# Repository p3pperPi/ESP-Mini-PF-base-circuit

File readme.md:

# 概要
ESP32を使用して、DCブラシモータを使用したライントレースをするための基板です。

# 回路図

# 機能
## 電源
J1の PHコネクタ、もしくは J3の XT60コネクタに電源を接続してください。
J1の PHコネクタを使用する際は、J2の PHコネクタにスイッチをつないでください。

入力可能な電圧の範囲はは ** 30V** です。

また、JP17をショートすることで、モータ電源にUSB 5Vを使用することが可能です。
ただし、JP17をショートした状態で電源コネクタに5V以外の電圧をかけると、接続した機器が破損します。
**JP17をショートさせた際は、絶対に電源コネクタから給電は行わないでください。**
なお、JP17にはダイオードを入れて逆流防止を行うことも可能です。その際は、[SBM245L](https://akizukidenshi.com/catalog/g/g117439/)を使用してください。

入力電源は、DCDCコンバータモジュール[CN39033A](https://japanese.alibaba.com/product-detail/CN3903-3A-Mini-Buck-Step-Down-1600380707339.html)を使用して5Vまで電圧を下げられます。

| 項目             | 値  | 単位 |
| ---------------- | --- | ---- |
| 最大定格入力電圧 | 30  | V    |
| 出力電流(Max.)   | 3   | A    |

上で生成された5Vから、[UZ1085L-22-TN3-R](https://www.lcsc.com/product-detail/Low-Dropout-Regulators-LDO_UZ1085L-AD-TN3-R_C146666.html)を使用し、マイコンへの電源供給を行います。
| 項目             | 値  | 単位 |
| ---------------- | --- | ---- |
| 最大定格入力電圧 | 18  | V    |
| 最大電流(Typ.)   | 4   | A |

## マイコン
ESP32-WROOM-32を使用します。  
[CH340X](https://www.lcsc.com/product-detail/USB-Converters_WCH-Jiangsu-Qin-Heng-CH340X_C3035748.html?s_z=n_CH340X)を使用した書き込み回路を持ちます。

## DCブラシモータ
モータドライバIC[CP3119MDTR](https://www.lcsc.com/product-detail/Brushed-DC-Motor-Drivers_XBLW-CP3119MDTR-XBLW_C42395499.html)を使用して、DCモータを制御します。

| 項目                  | 値       | 単位       |
| --------------------- | -------- | ---------- |
| 最大定格電圧          | 32       | V          |
| 最大定格電流          | 8.0      | A          |
| 推奨電源電圧範囲      | 3.0~30.0 | V          |
| 推奨最大電流          | 6.0      | A          |
| FETオン抵抗 (load=1A) | 80       | m $\Omega$ |
| FETオン抵抗 (load=3A) | 110      | m $\Omega$ |

## エンコーダ
A/B相のシングルエンドエンコーダをカウントします。エンコーダの電源電圧と信号入力は5Vです。
[TXB0104RUT](https://lcsc.com/product-detail/translators-level-shifters_texas-instruments-txb0104rutr_C105266.html)により、5V信号を3.3Vに変換してESP32に信号を入力します。
パルス入力ピンは、ソルダジャンパ(JP2 ~ 5)によりプルアップが可能です。
プルアップの有無については、[ジャンパの機能](#ジャンパの機能)を参照してください。

## 汎用IO
サーボモータ、センサ入力等のための、汎用のIOです。
ピンアサインは下記の通りです。

| ピン | 機能   |
| ---- | ------ |
| 1    | IOピン |
| 2    | Vs     |
| 3    | GND    |

ピン番号は、[ピンアサイン](#ピンアサイン)を参照してください。

Vsは、ソルダジャンパ(JP6 ~ 9)により電圧を選択可能です。
選択される電圧は、[ジャンパの機能](#ジャンパの機能)を参照してください。

## フォトリフレクタ
[ITR8307/S17/TR8(B)](https://www.lcsc.com/product-detail/Reflective-Optical-Interrupters_Everlight-Elec-ITR8307-S17-TR8-B_C81632.html?s_z=n_ITR8307-S17) を3つ搭載し、テープの判定を行います。

また、外付けのLED・フォトトランジスタを使用することも可能です。いずれも外形3mmの砲弾型のものを使用してください。

使用するフォトリフレクタの選択は、JP10～JP15 を使用してください。

## LED
3mm砲弾型LEDを4つ搭載可能です。  
D2は、電源投入時に点灯します。  
D3, D4, D5はESP32から点灯/消灯 を管理可能です。

# ピンアサイン

ESP32-WROOM-32のピンアサインは下記の通りです。

| ピン | IO pin          | 機能                 | IN/OUT       |
| ---- | --------------- | -------------------- | ------------ |
| 27   | IO16            | モータL出力1         | OUT (PWM)    |
| 28   | IO17            | モータL出力2         | OUT (PWM)    |
| 30   | IO18            | モータR出力1         | OUT (PWM)    |
| 31   | IO19            | モータR出力2         | OUT (PWM)    |
| 16   | IO13            | エンコーダL入力1     | IN (PWM)     |
| 13   | IO14            | エンコーダL入力2     | IN (PWM)     |
| 10   | IO25            | エンコーダR入力1     | IN (PWM)     |
| 11   | IO26            | エンコーダR入力2     | IN (PWM)     |
| 34   | IO3/RxD0        | PCとのUART RxD       | IN (COM.)    |
| 35   | IO1/TxD0        | PCとのUART TxD       | OUT (COM.)   |
| 25   | IO0             | Boot                 | -            |
| 9    | IO33            | ラインセンサ1        | IN(Analog)   |
| 6    | IO34            | ラインセンサ2        | IN(Analog)   |
| 8    | IO35            | ラインセンサ3        | IN(Analog)   |
| 33   | IO21            | LED 赤               | OUT(Digital) |
| 36   | IO22            | LED 黄               | OUT(Digital) |
| 37   | IO23            | LED 緑               | OUT(Digital) |
| 8    | IO32            | 汎用IO 0             | IN/OUT       |
| 12   | IO27            | 汎用IO 1             | IN/OUT       |
| 26   | IO4             | 汎用IO 2             | IN/OUT       |
| 29   | IO5             | 汎用IO 3(プルアップ) | IN/OUT       |
| 4    | IO36(SENSOR_VP) | 電源電圧監視(1/10)   | IN(Analog)   |

# ジャンパの機能

ジャンパにより、機能を切り替えることができます。

| ジャンパ | 機能             | モード1  | 機能1                                  | モード2  | 機能2                                 | デフォルト | 備考                                     |
| -------- | ---------------- | -------- | -------------------------------------- | -------- | ------------------------------------- | ---------- | ---------------------------------------- |
| JP1      | Power_SW_Disable | オープン | J2 パワースイッチが有効                | ショート | J2 パワースイッチが無効(常時ショート) | オープン   | -                                        |
| JP2      | L1_PU            | オープン | エンコーダL1の入力は電圧入力           | ショート | エンコーダL1の入力をプルアップ(1k)    | オープン   | -                                        |
| JP3      | L2_PU            | オープン | エンコーダL2の入力は電圧入力           | ショート | エンコーダL2の入力をプルアップ(1k)    | オープン   | -                                        |
| JP4      | R1_PU            | オープン | エンコーダR1の入力は電圧入力           | ショート | エンコーダR1の入力をプルアップ(1k)    | オープン   | -                                        |
| JP5      | R2_PU            | オープン | エンコーダR2の入力は電圧入力           | ショート | エンコーダR2の入力をプルアップ(1k)    | オープン   | -                                        |
| JP6      | Vs_SEL0          | 3.3      | 汎用入力J9 の2番ピンを3.3Vにする       | Vin      | 汎用入力J9 の2番ピンをVinにする       | オープン   | オープンだと2番ピンはNC                  |
| JP7      | Vs_SEL1          | 3.3      | 汎用入力J10 の2番ピンを3.3Vにする      | Vin      | 汎用入力J10 の2番ピンをVinにする      | オープン   | オープンだと2番ピンはNC                  |
| JP8      | Vs_SEL2          | 3.3      | 汎用入力J11 の2番ピンを3.3Vにする      | Vin      | 汎用入力J11 の2番ピンをVinにする      | オープン   | オープンだと2番ピンはNC                  |
| JP9      | Vs_SEL3          | 3.3      | 汎用入力J12 の2番ピンを3.3Vにする      | Vin      | 汎用入力J12 の2番ピンをVinにする      | オープン   | オープンだと2番ピンはNC                  |
| JP10     | LED_SEL1         | SMD      | ラインセンサ(U8)の LEDを有効化         | DIP      | D6 のLEDを有効化                      | オープン   | オープンだとU8, D6いずれのLEDも光らない  |
| JP11     | PT_SEL1          | SMD      | SENSOR1 の入力をラインセンサU8 にする  | DIP      | SENSOR1 の入力をQ1 にする             | オープン   | オープンだとSENSOR1 はN.C.               |
| JP12     | LED_SEL2         | SMD      | ラインセンサ(U9)の LEDを有効化         | DIP      | D7 のLEDを有効化                      | オープン   | オープンだとU9, D7いずれのLEDも光らない  |
| JP13     | PT_SEL2          | SMD      | SENSOR2 の入力をラインセンサU9 にする  | DIP      | SENSOR2 の入力をQ2 にする             | オープン   | オープンだとSENSOR2 はN.C.               |
| JP14     | LED_SEL2         | SMD      | ラインセンサ(U10)の LEDを有効化        | DIP      | D8 のLEDを有効化                      | オープン   | オープンだとU10, D8いずれのLEDも光らない |
| JP15     | PT_SEL2          | SMD      | SENSOR3 の入力をラインセンサU10 にする | DIP      | SENSOR3 の入力をQ1 にする             | オープン   | オープンだとSENSOR3 はN.C.               |
| JP16     | Reseet           | オープン | 通常動作                               | ショート | リセット                              | オープン   | スイッチ取付可                           |
| JP17     | USB＿Vs          | オープン | 外部電源をモータ電源とする             | ショート | USB電源をモータ電源とする             | オープン   | ショートの代わりにダイオードを使用可     |

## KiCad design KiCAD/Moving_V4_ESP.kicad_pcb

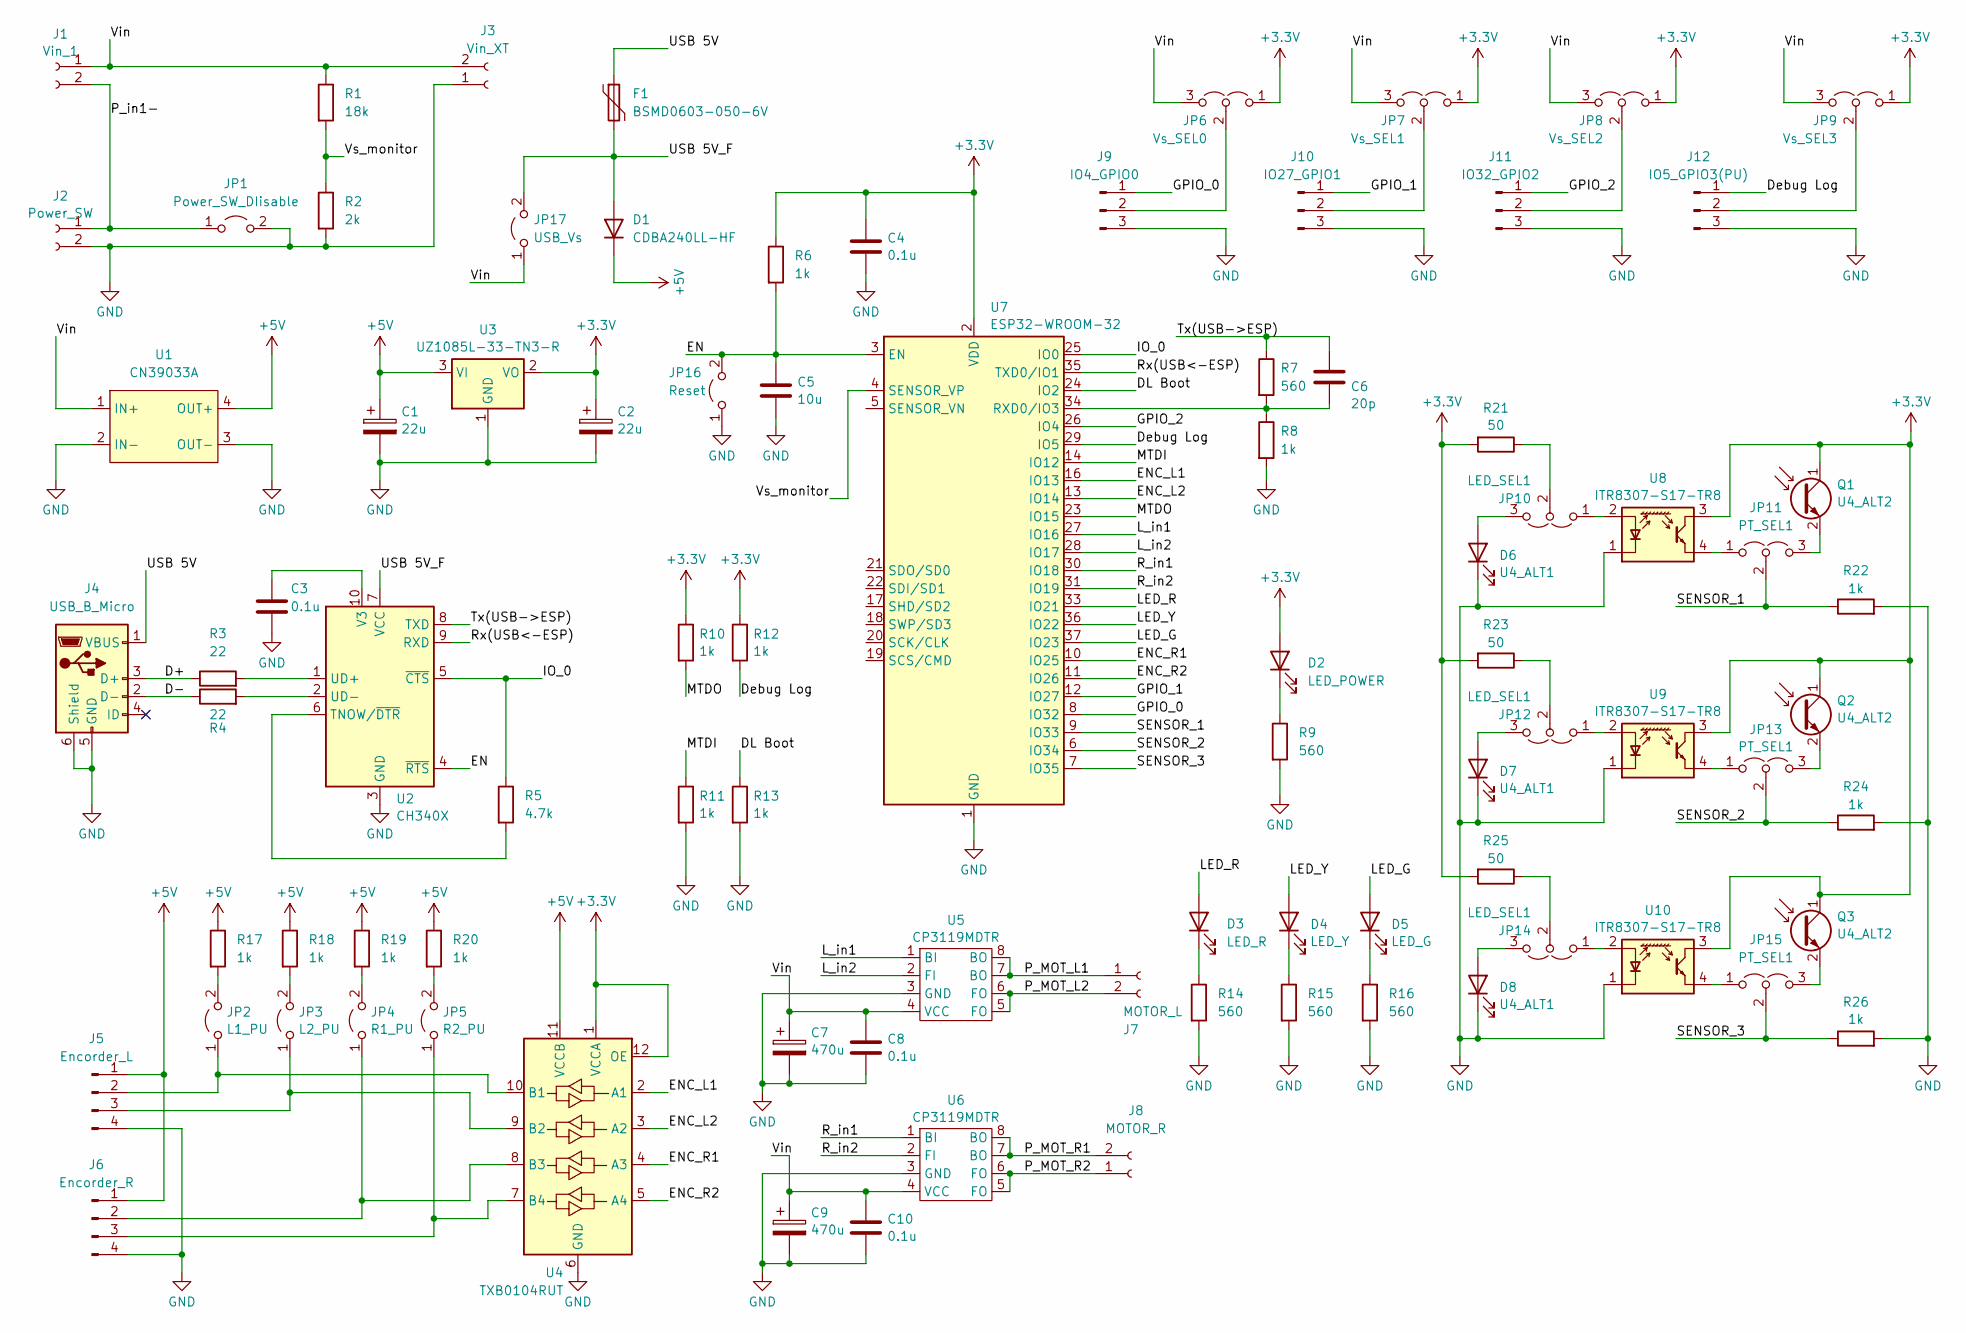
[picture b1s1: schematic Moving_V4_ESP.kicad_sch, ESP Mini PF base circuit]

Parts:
C1, C2: 22u; CP_Radial_D5.0mm_P2.00mm; LCSC x
C3, C4, C8, C10: 0.1u; C_0402_1005Metric; LCSC C77020
C5: 10u; C_0402_1005Metric; LCSC C76991
C6: 20p; C_0402_1005Metric; LCSC C76959
C7, C9: 470u; CP_Radial_D8.0mm_P3.50mm; LCSC x
D1: CDBA240LL-HF; D_SMA; LCSC C2886093
D2: LED_POWER; LED_D3.0mm; LCSC x
D3: LED_R; LED_D3.0mm; LCSC x
D4: LED_Y; LED_D3.0mm; LCSC x
D5: LED_G; LED_D3.0mm; LCSC x
D6, D7, D8: U4_ALT1; LED_D3.0mm; LCSC x
F1: BSMD0603-050-6V; Fuse_0603_1608Metric; LCSC C883095
J1: Vin_1; JST_PH_B2B-PH-K_1x02_P2.00mm_Vertical; LCSC x
J2: Power_SW; JST_PH_B2B-PH-K_1x02_P2.00mm_Vertical; LCSC x
J3: Vin_XT; AMASS_XT60-M_1x02_P7.20mm_Vertical; LCSC x
J4: USB_B_Micro; USB_Micro-B_Amphenol_10103594-0001LF_Horizontal; LCSC C428495
J5: Encorder_L; JST_ZH_B4B-ZH-A_1x04_P1.50mm_Vertical; LCSC x
J6: Encorder_R; JST_ZH_B4B-ZH-A_1x04_P1.50mm_Vertical; LCSC x
J7: MOTOR_L; TerminalBlock_bornier-2_P5.08mm; LCSC x
J8: MOTOR_R; TerminalBlock_bornier-2_P5.08mm; LCSC x
J9: IO4_GPIO0; PinHeader_1x03_P2.54mm_Vertical; LCSC x
J10: IO27_GPIO1; PinHeader_1x03_P2.54mm_Vertical; LCSC x
J11: IO32_GPIO2; PinHeader_1x03_P2.54mm_Vertical; LCSC x
J12: IO5_GPIO3(PU); PinHeader_1x03_P2.54mm_Vertical; LCSC x
JP1: Power_SW_DIisable; SolderJumper-2_P1.3mm_Open_RoundedPad1.0x1.5mm; LCSC x
JP2: L1_PU; SolderJumper-2_P1.3mm_Open_RoundedPad1.0x1.5mm; LCSC x
JP3: L2_PU; SolderJumper-2_P1.3mm_Open_RoundedPad1.0x1.5mm; LCSC x
JP4: R1_PU; SolderJumper-2_P1.3mm_Open_RoundedPad1.0x1.5mm; LCSC x
JP5: R2_PU; SolderJumper-2_P1.3mm_Open_RoundedPad1.0x1.5mm; LCSC x
JP6: Vs_SEL0; SolderJumper-3_P1.3mm_Open_RoundedPad1.0x1.5mm; LCSC x
JP7: Vs_SEL1; SolderJumper-3_P1.3mm_Open_RoundedPad1.0x1.5mm; LCSC x
JP8: Vs_SEL2; SolderJumper-3_P1.3mm_Open_RoundedPad1.0x1.5mm; LCSC x
JP9: Vs_SEL3; SolderJumper-3_P1.3mm_Open_RoundedPad1.0x1.5mm; LCSC x
JP10, JP12, JP14: LED_SEL1; SolderJumper-3_P1.3mm_Open_RoundedPad1.0x1.5mm; LCSC x
JP11, JP13, JP15: PT_SEL1; SolderJumper-3_P1.3mm_Open_RoundedPad1.0x1.5mm; LCSC x
JP16: Reset; SolderJumper-2_TVAF06-A020B-R_COMPATIBLE; LCSC x
JP17: USB_Vs; D_DO-41_SOD81_P7.62mm_Horizontal; LCSC x
Q1, Q2, Q3: U4_ALT2; LED_D3.0mm; LCSC x
R1: 18k; R_0402_1005Metric; LCSC C316875
R2: 2k; R_0402_1005Metric; LCSC C173345
R3, R4: 22; R_0402_1005Metric; LCSC C400511
R5: 4.7k; R_0402_1005Metric; LCSC C159885
R6, R8, R10, R11, R12, R13, R17, R18, R19, R20, R22, R24, R26: 1k; R_0402_1005Metric; LCSC C159872
R7, R9, R14, R15, R16: 560; R_0402_1005Metric; LCSC C427239
R21, R23, R25: 50; R_0805_2012Metric; LCSC C2828866
U1: CN39033A; DCDC_Conv_CN39033A; LCSC x
U2: CH340X; MSOP-10_3x3mm_P0.5mm; LCSC C3035748
U3: UZ1085L-33-TN3-R; TO-252-2; LCSC C125622
U4: TXB0104RUT; Texas_R-PUQFN-N12; LCSC C105266
U5, U6: CP3119MDTR; SOP-8_3.9x4.9mm_P1.27mm; LCSC C42395499
U7: ESP32-WROOM-32; ESP32-WROOM-32_39P-TH; LCSC x
U8, U9, U10: ITR8307-S17-TR8; Everlight_ITR1201SR10AR; LCSC C81632

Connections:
+3.3V: C2.1, C4.1, D2.2 (A), JP6.1 (A), JP7.1 (A), JP8.1 (A), JP9.1 (A), Q1.1 (C), Q2.1 (C), Q3.1 (C), R6.1, R10.1, R12.1, R21.2, R23.2, R25.2, U3.2 (VO), U4.1 (VCCA), U4.12 (OE), U7.2 (VDD), U8.3, U9.3, U10.3
+5V: C1.1, D1.1 (K), J5.1, J6.1, R17.1, R18.1, R19.1, R20.1, U1.4 (OUT+), U3.3 (VI), U4.11 (VCCB)
/D+: J4.3 (D+), R3.1
/D-: J4.2 (D-), R4.1
/DL Boot: R13.1, U7.24 (IO2)
/Debug Log: J12.1, R12.2, U7.29 (IO5)
/EN: C5.1, JP16.2 (B), R6.2, U2.4 (~RTS), U7.3 (EN)
/ENC_L1: U4.2 (A1), U7.16 (IO13)
/ENC_L2: U4.3 (A2), U7.13 (IO14)
/ENC_R1: U4.4 (A3), U7.10 (IO25)
/ENC_R2: U4.5 (A4), U7.11 (IO26)
/GPIO_0: J9.1, U7.8 (IO32)
/GPIO_1: J10.1, U7.12 (IO27)
/GPIO_2: J11.1, U7.26 (IO4)
/IO_0: R5.1, U2.5 (~CTS), U7.25 (IO0)
/LED_G: D5.2 (A), U7.37 (IO23)
/LED_R: D3.2 (A), U7.33 (IO21)
/LED_Y: D4.2 (A), U7.36 (IO22)
/L_in1: U5.1 (BI), U7.27 (IO16)
/L_in2: U5.2 (FI), U7.28 (IO17)
/MTDI: R11.1, U7.14 (IO12)
/MTDO: R10.2, U7.23 (IO15)
/P_MOT_L1: J7.1, U5.7 (BO), U5.8 (BO)
/P_MOT_L2: J7.2, U5.5 (FO), U5.6 (FO)
/P_MOT_R1: J8.2, U6.7 (BO), U6.8 (BO)
/P_MOT_R2: J8.1, U6.5 (FO), U6.6 (FO)
/P_in1-: J1.2, J2.1, JP1.1 (A)
/R_in1: U6.1 (BI), U7.30 (IO18)
/R_in2: U6.2 (FI), U7.31 (IO19)
/Rx(USB<-ESP): U2.9 (RXD), U7.35 (TXD0/IO1)
/SENSOR_1: JP11.2 (C), R22.1, U7.9 (IO33)
/SENSOR_2: JP13.2 (C), R24.1, U7.6 (IO34)
/SENSOR_3: JP15.2 (C), R26.1, U7.7 (IO35)
/Tx(USB->ESP): C6.1, R7.1, U2.8 (TXD)
/USB 5V: F1.1, J4.1 (VBUS)
/USB 5V_F: D1.2 (A), F1.2, JP17.2 (B), U2.7 (VCC)
/Vin: C7.1, C8.1, C9.1, C10.1, J1.1, J3.2, JP6.3 (B), JP7.3 (B), JP8.3 (B), JP9.3 (B), JP17.1 (A), R1.1, U1.1 (IN+), U5.4 (VCC), U6.4 (VCC)
/Vs_monitor: R1.2, R2.1, U7.4 (SENSOR_VP)
GND: C1.2, C2.2, C3.2, C4.2, C5.2, C7.2, C8.2, C9.2, C10.2, D6.1 (K), D7.1 (K), D8.1 (K), J2.2, J3.1, J4.5 (GND), J4.6 (Shield), J5.4, J6.4, J9.3, J10.3, J11.3, J12.3, JP1.2 (B), JP16.1 (A), R2.2, R8.2, R9.2, R11.2, R13.2, R14.2, R15.2, R16.2, R22.2, R24.2, R26.2, U1.2 (IN-), U1.3 (OUT-), U2.3 (GND), U3.1 (GND), U4.6 (GND), U5.3 (GND), U6.3 (GND), U7.1 (GND), U7.15 (GND), U7.38 (GND), U7.39 (GND), U8.1 (K), U9.1 (K), U10.1 (K)
unnamed: D2.1 (K), R9.1
unnamed: D3.1 (K), R14.1
unnamed: D4.1 (K), R15.1
unnamed: D5.1 (K), R16.1
unnamed: D6.2 (A), JP10.3 (B)
unnamed: D7.2 (A), JP12.3 (B)
unnamed: D8.2 (A), JP14.3 (B)
unnamed: J5.2, JP2.1 (A), U4.10 (B1)
unnamed: J5.3, JP3.1 (A), U4.9 (B2)
unnamed: J6.2, JP4.1 (A), U4.8 (B3)
unnamed: J6.3, JP5.1 (A), U4.7 (B4)
unnamed: J9.2, JP6.2 (C)
unnamed: J10.2, JP7.2 (C)
unnamed: J11.2, JP8.2 (C)
unnamed: J12.2, JP9.2 (C)
unnamed: JP2.2 (B), R17.2
unnamed: JP3.2 (B), R18.2
unnamed: JP4.2 (B), R19.2
unnamed: JP5.2 (B), R20.2
unnamed: JP10.1 (A), U8.2 (A)
unnamed: JP10.2 (C), R21.1
unnamed: JP11.1 (A), U8.4
unnamed: JP11.3 (B), Q1.2 (E)
unnamed: JP12.1 (A), U9.2 (A)
unnamed: JP12.2 (C), R23.1
unnamed: JP13.1 (A), U9.4
unnamed: JP13.3 (B), Q2.2 (E)
unnamed: JP14.1 (A), U10.2 (A)
unnamed: JP14.2 (C), R25.1
unnamed: JP15.1 (A), U10.4
unnamed: JP15.3 (B), Q3.2 (E)
unnamed: R5.2, U2.6 (TNOW/~DTR)
unnamed: R3.2, U2.1 (UD+)
unnamed: R4.2, U2.2 (UD-)
unnamed: C3.1, U2.10 (V3)
unnamed: C6.2, R7.2, R8.1, U7.34 (RXD0/IO3)

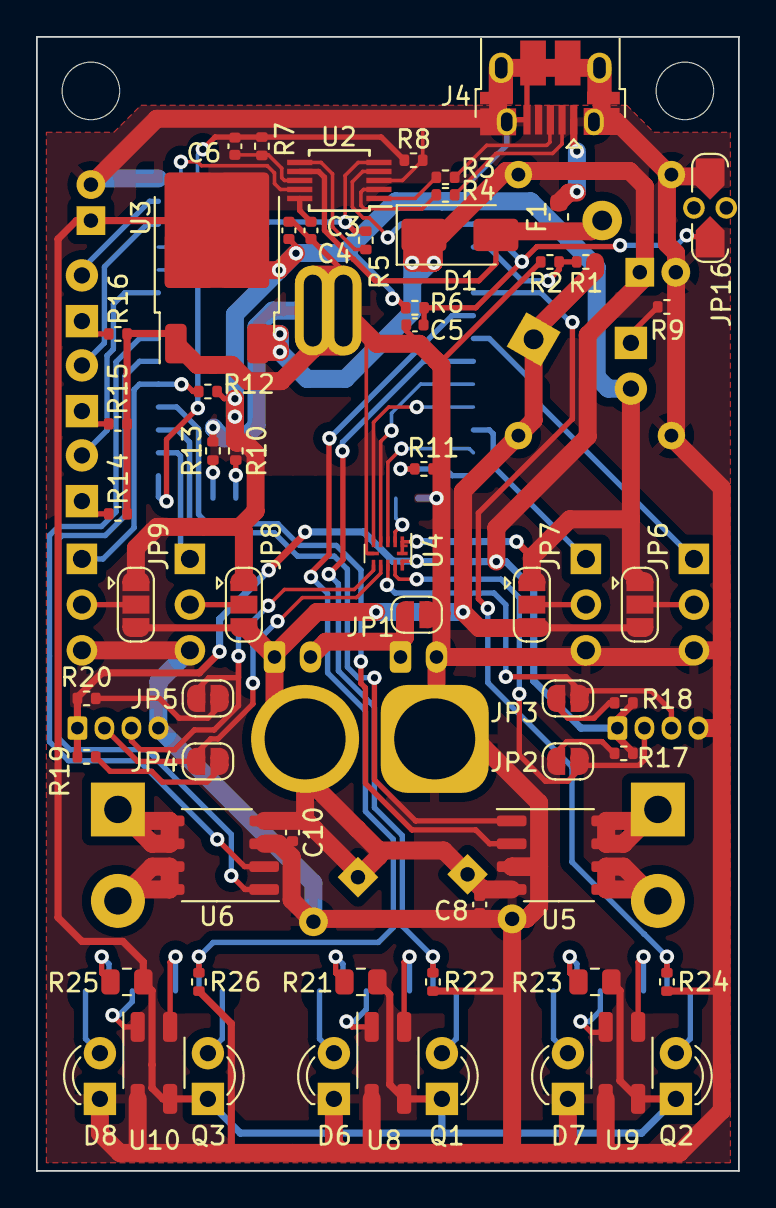
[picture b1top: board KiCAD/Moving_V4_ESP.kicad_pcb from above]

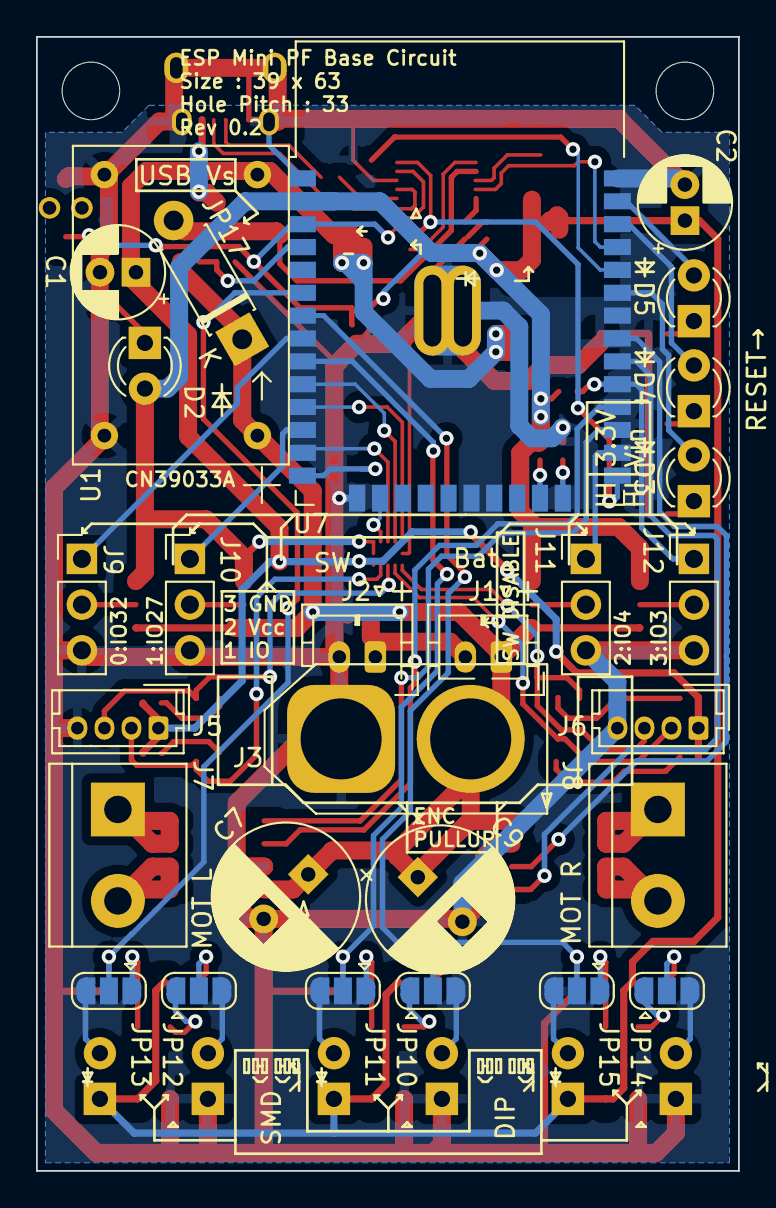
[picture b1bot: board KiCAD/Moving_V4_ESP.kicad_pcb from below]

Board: 2 copper layers, 39.0 x 63.0 mm, 87 parts (28 on the bottom side), 75 nets.

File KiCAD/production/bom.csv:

Designator,Footprint,Quantity,Value,LCSC Part #
"C1, C2",CP_Radial_D5.0mm_P2.00mm,2,22u,x
"C10, C3, C4, C8",0402,4,0.1u,C77020
C5,0402,1,10u,C76991
C6,0402,1,20p,C76959
"C7, C9",CP_Radial_D8.0mm_P3.50mm,2,470u,x
D1,D_SMA,1,CDBA240LL-HF,C2886093
D2,LED_D3.0mm,1,LED_POWER,x
D3,LED_D3.0mm,1,LED_R,x
D4,LED_D3.0mm,1,LED_Y,x
D5,LED_D3.0mm,1,LED_G,x
"D6, D7, D8",LED_D3.0mm,3,U4_ALT1,x
F1,0603,1,"BSMD0603-050-6V
",C883095
J1,JST_PH_B2B-PH-K_1x02_P2.00mm_Vertical,1,Vin_1,x
J10,PinHeader_1x03_P2.54mm_Vertical,1,IO27_GPIO1,x
J11,PinHeader_1x03_P2.54mm_Vertical,1,IO32_GPIO2,x
J12,PinHeader_1x03_P2.54mm_Vertical,1,IO5_GPIO3(PU),x
J2,JST_PH_B2B-PH-K_1x02_P2.00mm_Vertical,1,Power_SW,x
J3,AMASS_XT60-M_1x02_P7.20mm_Vertical,1,Vin_XT,x
J4,USB_Micro-B_Amphenol_10103594-0001LF_Horizontal,1,USB_B_Micro,C428495
J5,JST_ZH_B4B-ZH-A_1x04_P1.50mm_Vertical,1,Encorder_L,x
J6,JST_ZH_B4B-ZH-A_1x04_P1.50mm_Vertical,1,Encorder_R,x
J7,TerminalBlock_bornier-2_P5.08mm,1,MOTOR_L,x
J8,TerminalBlock_bornier-2_P5.08mm,1,MOTOR_R,x
J9,PinHeader_1x03_P2.54mm_Vertical,1,IO4_GPIO0,x
JP1,SolderJumper-2_P1.3mm_Open_RoundedPad1.0x1.5mm,1,Power_SW_DIisable,x
"JP10, JP12, JP14",SolderJumper-3_P1.3mm_Open_RoundedPad1.0x1.5mm,3,LED_SEL1,x
"JP11, JP13, JP15",SolderJumper-3_P1.3mm_Open_RoundedPad1.0x1.5mm,3,PT_SEL1,x
JP16,SolderJumper-2_TVAF06-A020B-R_COMPATIBLE,1,Reset,x
JP17,D_DO-41_SOD81_P7.62mm_Horizontal,1,USB_Vs,x
JP2,SolderJumper-2_P1.3mm_Open_RoundedPad1.0x1.5mm,1,L1_PU,x
JP3,SolderJumper-2_P1.3mm_Open_RoundedPad1.0x1.5mm,1,L2_PU,x
JP4,SolderJumper-2_P1.3mm_Open_RoundedPad1.0x1.5mm,1,R1_PU,x
JP5,SolderJumper-2_P1.3mm_Open_RoundedPad1.0x1.5mm,1,R2_PU,x
JP6,SolderJumper-3_P1.3mm_Open_RoundedPad1.0x1.5mm,1,Vs_SEL0,x
JP7,SolderJumper-3_P1.3mm_Open_RoundedPad1.0x1.5mm,1,Vs_SEL1,x
JP8,SolderJumper-3_P1.3mm_Open_RoundedPad1.0x1.5mm,1,Vs_SEL2,x
JP9,SolderJumper-3_P1.3mm_Open_RoundedPad1.0x1.5mm,1,Vs_SEL3,x
"Q1, Q2, Q3",LED_D3.0mm,3,U4_ALT2,x
R1,0402,1,18k,C316875
"R10, R11, R12, R13, R17, R18, R19, R20, R22, R24, R26, R6, R8",0402,13,1k,C159872
"R14, R15, R16, R7, R9",0402,5,560,C427239
R2,0402,1,2k,C173345
"R21, R23, R25",0805,3,50,C2828866
"R3, R4",0402,2,22,C400511
R5,0402,1,4.7k,C159885
U1,DCDC_Conv_CN39033A,1,CN39033A,x
"U10, U8, U9",Everlight_ITR1201SR10AR,3,ITR8307-S17-TR8,C81632
U2,MSOP-10_3x3mm_P0.5mm,1,CH340X,C3035748
U3,TO-252-2,1,UZ1085L-33-TN3-R,C125622
U4,Texas_R-PUQFN-N12,1,TXB0104RUT,C105266
"U5, U6",SOP-8_3.9x4.9mm_P1.27mm,2,CP3119MDTR,C42395499
U7,ESP32-WROOM-32_39P-TH,1,ESP32-WROOM-32,x

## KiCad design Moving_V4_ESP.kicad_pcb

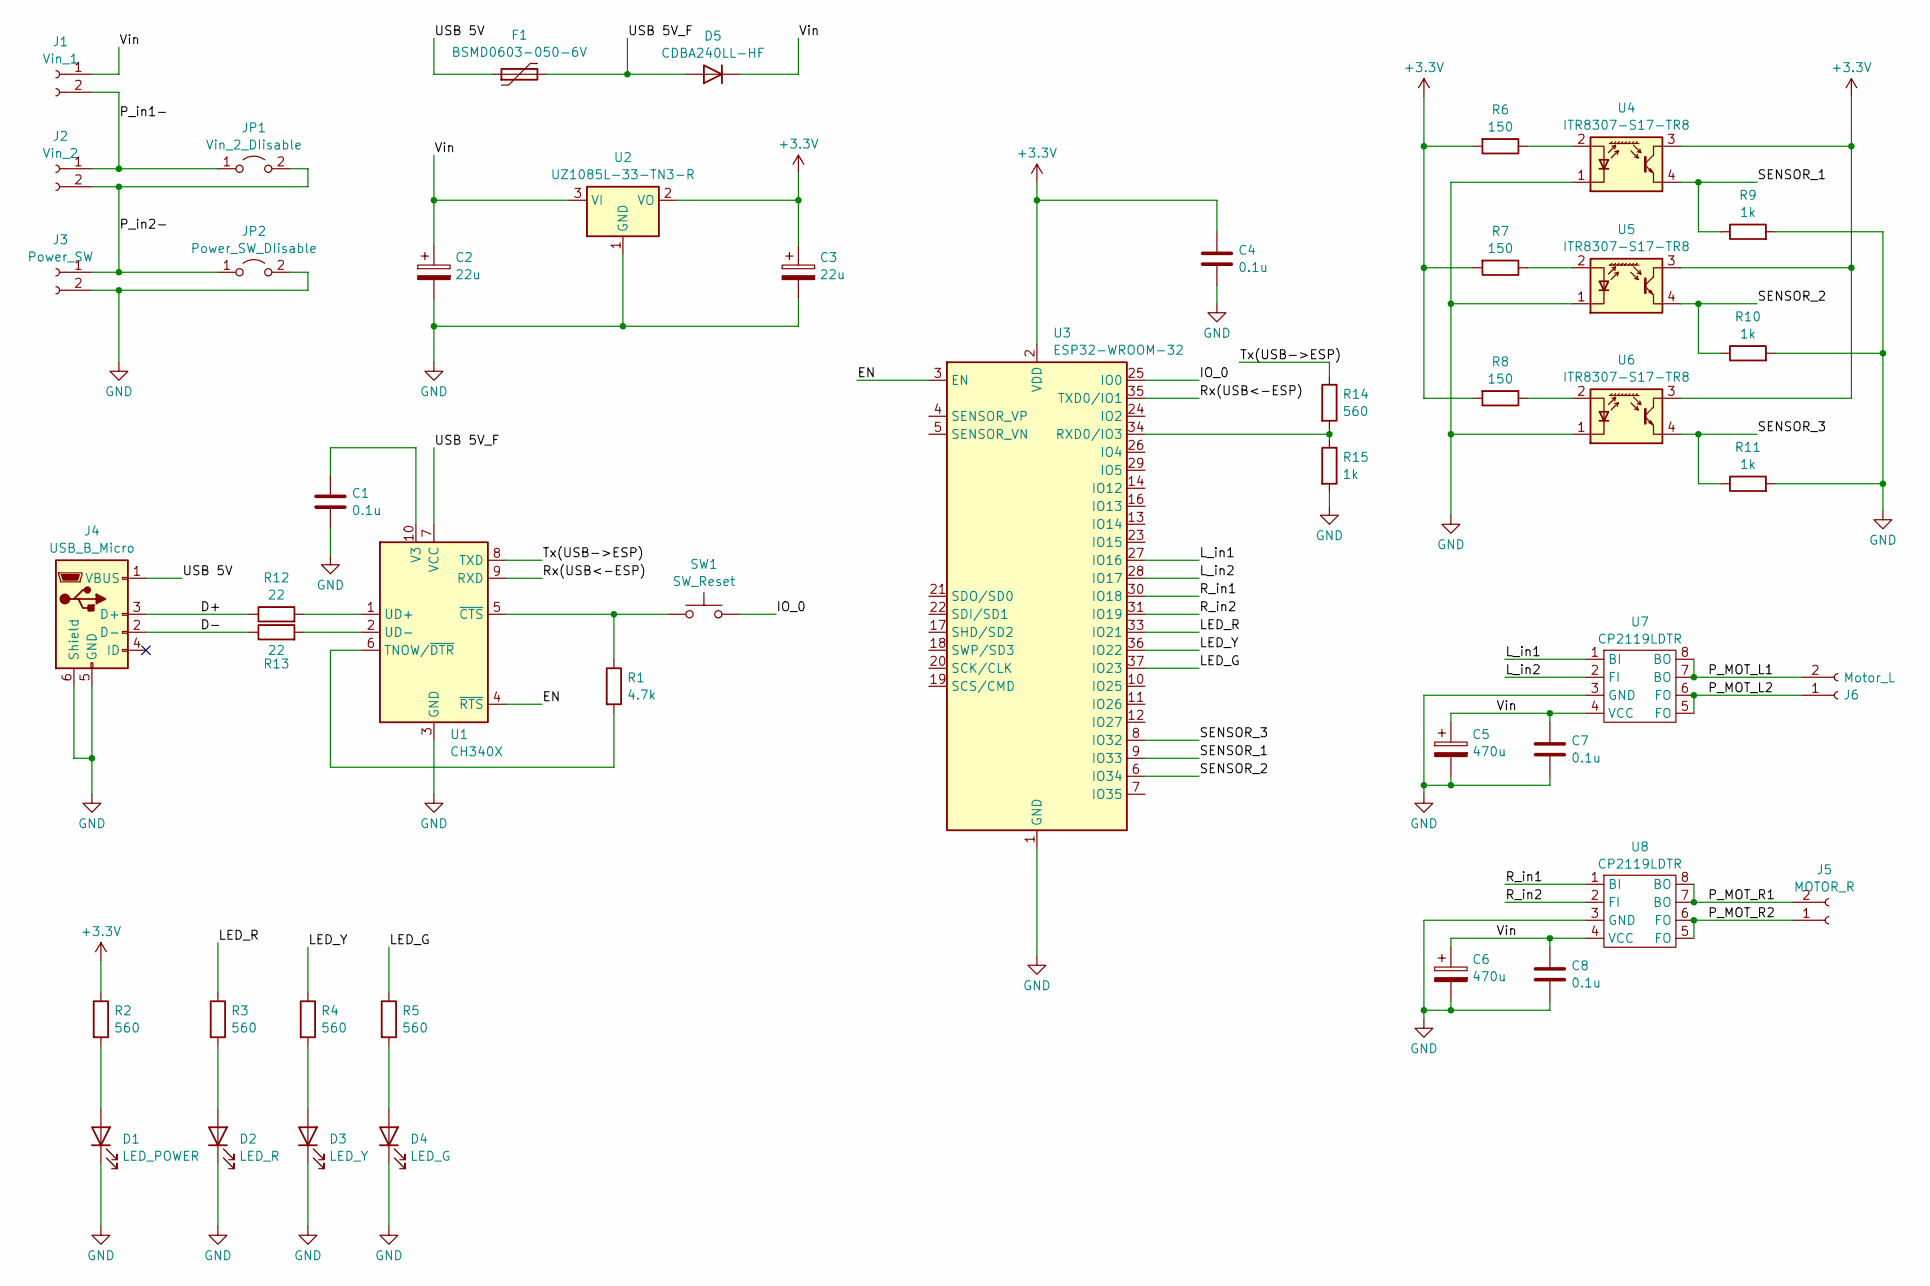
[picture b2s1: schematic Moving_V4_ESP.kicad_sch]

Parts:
C1, C4, C7, C8: 0.1u; C_0402_1005Metric; LCSC C77020
C2, C3: 22u; CP_Elec_6.3x5.4; LCSC C131161
C5, C6: 470u; CP_Radial_D8.0mm_P3.50mm; LCSC x
D1: LED_POWER; LED_D3.0mm; LCSC x
D2: LED_R; LED_D3.0mm; LCSC x
D3: LED_Y; LED_D3.0mm; LCSC x
D4: LED_G; LED_D3.0mm; LCSC x
D5: CDBA240LL-HF; D_SMA; LCSC C2886093
F1: BSMD0603-050-6V; Fuse_0603_1608Metric; LCSC C883095
J1: Vin_1; JST_PH_B2B-PH-K_1x02_P2.00mm_Vertical; LCSC C160352
J2: Vin_2; JST_PH_B2B-PH-K_1x02_P2.00mm_Vertical; LCSC C160352
J3: Power_SW; JST_PH_B2B-PH-K_1x02_P2.00mm_Vertical; LCSC C160352
J4: USB_B_Micro; USB_Micro-B_Amphenol_10103594-0001LF_Horizontal; LCSC C428495
J5: MOTOR_R; TerminalBlock_bornier-2_P5.08mm; LCSC C8465
J6: Motor_L; TerminalBlock_bornier-2_P5.08mm; LCSC C8465
JP1: Vin_2_DIisable; SolderJumper-2_P1.3mm_Open_RoundedPad1.0x1.5mm; LCSC x
JP2: Power_SW_DIisable; SolderJumper-2_P1.3mm_Open_RoundedPad1.0x1.5mm; LCSC x
R1: 4.7k; R_0402_1005Metric; LCSC C159885
R2, R3, R4, R5, R14: 560; R_0402_1005Metric; LCSC C427239
R6, R7, R8: 150; R_0402_1005Metric; LCSC C159952
R9, R10, R11, R15: 1k; R_0402_1005Metric; LCSC C159872
R12, R13: 22; R_0402_1005Metric; LCSC C400511
SW1: SW_Reset; SW_Push_1P1T_XKB_TS-1187A; LCSC C318884
U1: CH340X; MSOP-10_3x3mm_P0.5mm; LCSC C3035748
U2: UZ1085L-33-TN3-R; TO-252-2; LCSC C125622
U3: ESP32-WROOM-32
U4, U5, U6: ITR8307-S17-TR8; Everlight_ITR1201SR10AR; LCSC C81632
U7, U8: CP2119LDTR; SOP-8_3.9x4.9mm_P1.27mm; LCSC C42395498

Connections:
+3.3V: C3.1, C4.1, R2.1, R6.2, R7.2, R8.2, U2.2 (VO), U3.2 (VDD), U4.3, U5.3, U6.3
/D+: J4.3 (D+), R12.1
/D-: J4.2 (D-), R13.1
/EN: U1.4 (~RTS), U3.3 (EN)
/IO_0: SW1.2, U3.25 (IO0)
/LED_G: R5.1, U3.37 (IO23)
/LED_R: R3.1, U3.33 (IO21)
/LED_Y: R4.1, U3.36 (IO22)
/L_in1: U3.27 (IO16), U7.1 (BI)
/L_in2: U3.28 (IO17), U7.2 (FI)
/P_MOT_L1: J6.2, U7.7 (BO), U7.8 (BO)
/P_MOT_L2: J6.1, U7.5 (FO), U7.6 (FO)
/P_MOT_R1: J5.2, U8.7 (BO), U8.8 (BO)
/P_MOT_R2: J5.1, U8.5 (FO), U8.6 (FO)
/P_in1-: J1.2, J2.1, JP1.1 (A)
/P_in2-: J2.2, J3.1, JP1.2 (B), JP2.1 (A)
/R_in1: U3.30 (IO18), U8.1 (BI)
/R_in2: U3.31 (IO19), U8.2 (FI)
/Rx(USB<-ESP): U1.9 (RXD), U3.35 (TXD0/IO1)
/SENSOR_1: R9.1, U3.9 (IO33), U4.4
/SENSOR_2: R10.1, U3.6 (IO34), U5.4
/SENSOR_3: R11.1, U3.8 (IO32), U6.4
/Tx(USB->ESP): R14.1, U1.8 (TXD)
/USB 5V: F1.1, J4.1 (VBUS)
/USB 5V_F: D5.2 (A), F1.2, U1.7 (VCC)
/Vin: C2.1, C5.1, C6.1, C7.1, C8.1, D5.1 (K), J1.1, U2.3 (VI), U7.4 (VCC), U8.4 (VCC)
GND: C1.2, C2.2, C3.2, C4.2, C5.2, C6.2, C7.2, C8.2, D1.1 (K), D2.1 (K), D3.1 (K), D4.1 (K), J3.2, J4.5 (GND), J4.6 (Shield), JP2.2 (B), R9.2, R10.2, R11.2, R15.2, U1.3 (GND), U2.1 (GND), U3.1 (GND), U3.15 (GND), U3.38 (GND), U3.39 (GND), U4.1 (K), U5.1 (K), U6.1 (K), U7.3 (GND), U8.3 (GND)
unnamed: D1.2 (A), R2.2
unnamed: D2.2 (A), R3.2
unnamed: D3.2 (A), R4.2
unnamed: D4.2 (A), R5.2
unnamed: R1.2, U1.6 (TNOW/~DTR)
unnamed: R12.2, U1.1 (UD+)
unnamed: R13.2, U1.2 (UD-)
unnamed: C1.1, U1.10 (V3)
unnamed: R1.1, SW1.1, U1.5 (~CTS)
unnamed: R14.2, R15.1, U3.34 (RXD0/IO3)
unnamed: R6.1, U4.2 (A)
unnamed: R7.1, U5.2 (A)
unnamed: R8.1, U6.2 (A)

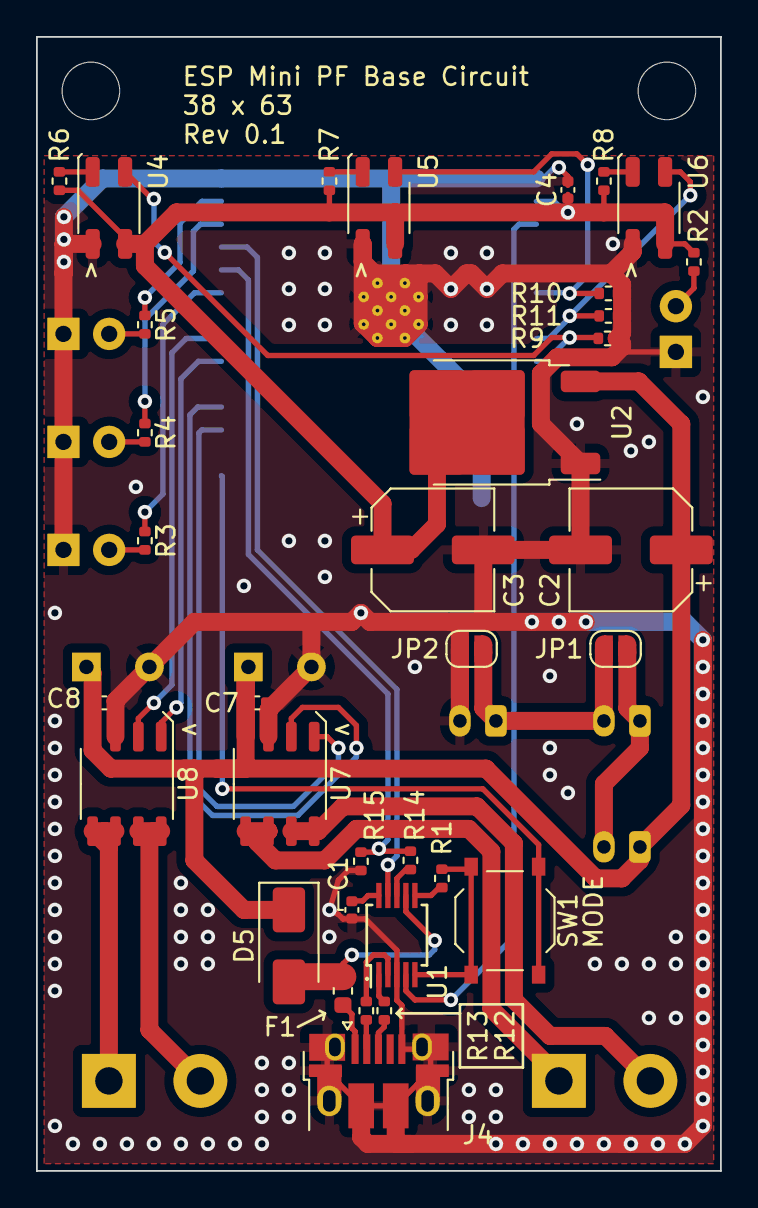
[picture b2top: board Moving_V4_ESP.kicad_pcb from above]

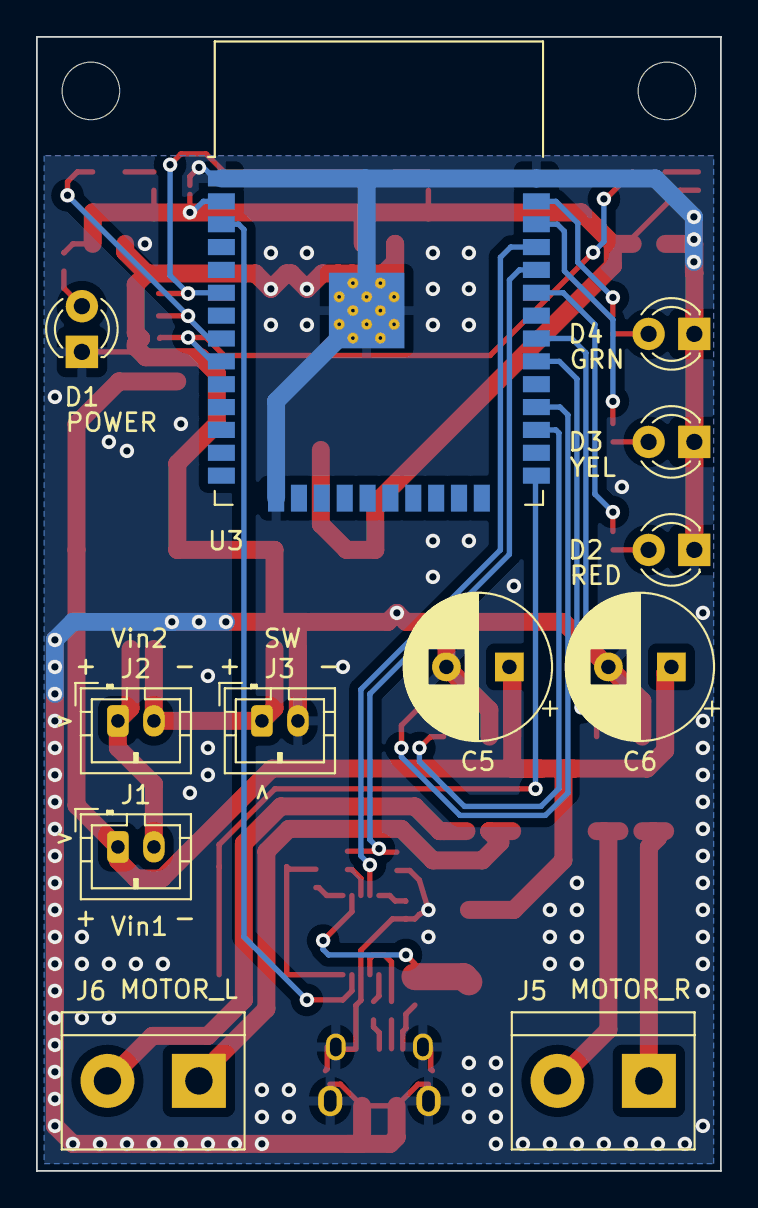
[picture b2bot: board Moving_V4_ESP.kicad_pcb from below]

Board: 2 copper layers, 38.0 x 63.0 mm, 46 parts (12 on the bottom side), 40 nets.

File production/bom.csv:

Designator,Footprint,Quantity,Value,LCSC Part #
"C1, C4, C7, C8",0402,4,0.1u,C77020
"C2, C3",CP_Elec_6.3x5.4,2,22u,C131161
"C5, C6",CP_Radial_D8.0mm_P3.50mm,2,470u,x
D1,LED_D3.0mm,1,LED_POWER,x
D2,LED_D3.0mm,1,LED_R,x
D3,LED_D3.0mm,1,LED_Y,x
D4,LED_D3.0mm,1,LED_G,x
D5,D_SMA,1,CDBA240LL-HF,C2886093
F1,0603,1,"BSMD0603-050-6V
",C883095
J1,JST_PH_B2B-PH-K_1x02_P2.00mm_Vertical,1,Vin_1,C160352
J2,JST_PH_B2B-PH-K_1x02_P2.00mm_Vertical,1,Vin_2,C160352
J3,JST_PH_B2B-PH-K_1x02_P2.00mm_Vertical,1,Power_SW,C160352
J4,USB_Micro-B_Amphenol_10103594-0001LF_Horizontal,1,USB_B_Micro,C428495
J5,TerminalBlock_bornier-2_P5.08mm,1,MOTOR_R,C8465
J6,TerminalBlock_bornier-2_P5.08mm,1,Motor_L,C8465
JP1,SolderJumper-2_P1.3mm_Open_RoundedPad1.0x1.5mm,1,Vin_2_DIisable,x
JP2,SolderJumper-2_P1.3mm_Open_RoundedPad1.0x1.5mm,1,Power_SW_DIisable,x
R1,0402,1,4.7k,C159885
"R10, R11, R15, R9",0402,4,1k,C159872
"R12, R13",0402,2,22,C400511
"R14, R2, R3, R4, R5",0402,5,560,C427239
"R6, R7, R8",0402,3,150,C159952
SW1,SW_Push_1P1T_XKB_TS-1187A,1,SW_Reset,C318884
U1,MSOP-10_3x3mm_P0.5mm,1,CH340X,C3035748
U2,TO-252-2,1,UZ1085L-33-TN3-R,C125622
U3,ESP32-WROOM-32,1,ESP32-WROOM-32,-
"U4, U5, U6",Everlight_ITR1201SR10AR,3,ITR8307-S17-TR8,C81632
"U7, U8",SOP-8_3.9x4.9mm_P1.27mm,2,CP2119LDTR,C42395498

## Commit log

2025-04-27 v0.1 基板のデータを追加
2025-04-27 キャッシュファイルをトラッキングから削除
2025-04-27 gitignoreを追加
2025-04-27 版を追加
2025-04-27 出力した回路図を追加
2025-04-27 readmeを追加
2025-04-27 フォルダ階層を変更
2025-04-29 表の誤りを更新
2025-05-05 ピンアサインの定義ファイルを追加
2025-05-05 LED点灯のテストプログラムを追加
2025-05-05 モータのテストプログラムを追加
2025-05-05 シリアル通信のテストプログラムを作成
2025-05-05 フォトリフレクタのテストプログラムを追加
2025-05-05 ブラウザで表示するUIのテストプログラムを作成
2025-05-06 LittleFSのサンプルプログラムを追加
2025-05-06 ラジコン操作のベースプログラムを追加
2025-05-10 UART分圧抵抗にコンデンサを追加
2025-05-10 フォトリフレクタのLED電流制限抵抗を50Ωに変更
2025-05-10 フォトリフレクタをジャンパで選択できるように変更
2025-05-18 機能ピンのプルアップ・プルダウンを追加
2025-05-18 5Vの系列を追加
2025-05-19 エンコーダ回路を追加(仮、要レベルコンバータ)
2025-05-20 エンコーダ入力回路にレベルシフタを追加
2025-05-20 汎用IOを追加。回路図はいったんシート外に記載。GPIO3にはDebug Logピンを使用
2025-05-22 汎用IOのフットプリントを反映
2025-05-22 エンコーダコネクタをZHに変更
2025-05-22 入力専用ピンがGPIOに割り振られていたため、センサ入力ピンと交換
2025-05-23 電源電圧監視回路を追加
2025-05-23 不要な抵抗を削除
2025-05-23 モータドライバの部品名を修正
2025-05-26 回路図がシートに収まるようにレイアウト調整
2025-05-26 電源コネクタを一つ削除
2025-05-27 アノテーションを再実行
2025-05-28 モード切替スイッチを削除
2025-05-29 リセット用のジャンパー追加
2025-05-29 電解コンデンサをDIP部品に変更
2025-05-30 部品表に秋月の商品コードを追加
2025-05-30 USB電源でモータを回すためのジャンパを追加
2025-05-31 リセット用じジャンパをSMDスイッチが取り付けできる形に変更
2025-06-01 ESP32のフットプリントを、背面パッドが裏面からはんだ付けできる形に変更
2025-06-08 5VのDCDCコンバータを変更
2025-06-08 回路図の版を更新
2025-06-08 回路図を出力
2025-06-08 Revのテキストを更新
2025-06-08 主要部品をロック
2025-06-12 JP17のフットプリントをにDO41ダイオードが取付できる形に変更
2025-06-14 誤ったジャンクションを削除
2025-06-14 レイアウト都合での回路修正
2025-06-14 部品を仮配置
2025-06-15 レイアウト都合でのピンアサイン変更
2025-06-15 レイアウトを仮配線
2025-06-16 基本的なシルクを配置
2025-06-16 シルク・塗りつぶりを調整
2025-06-17 更新日を更新
2025-06-17 回路図をエクスポート
2025-06-17 版を記入
2025-06-17 プロジェクトファイルを更新
2025-06-17 製造データを出力
2025-06-19 readmeを更新
2025-06-19 EPS32S3をサポートから削除
2025-06-21 ピンアサインを最新のものに修正
2025-06-21 ピン定義ファイルを更新
2025-06-21 S3のピン設定ファイルのインクルードを削除
2025-06-29 3Dモデルを追加
2025-06-29 モータ制御のサンプルを追加(エンコーダ読み取りまで記述)
2025-07-06 モータ制御のサンプルに速度平均を算出する処理を追加
2025-07-06 モータ制御のサンプルに速度制御の処理を追加
